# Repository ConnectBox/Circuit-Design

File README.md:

# Circuit-Design
Connectbox Circuit Design

This repo contains the schematic and KiCAD design files for the NEO-USB-HAT.  This is a daugherboard to add an extra USB port and power input to a NanoPi NEO.

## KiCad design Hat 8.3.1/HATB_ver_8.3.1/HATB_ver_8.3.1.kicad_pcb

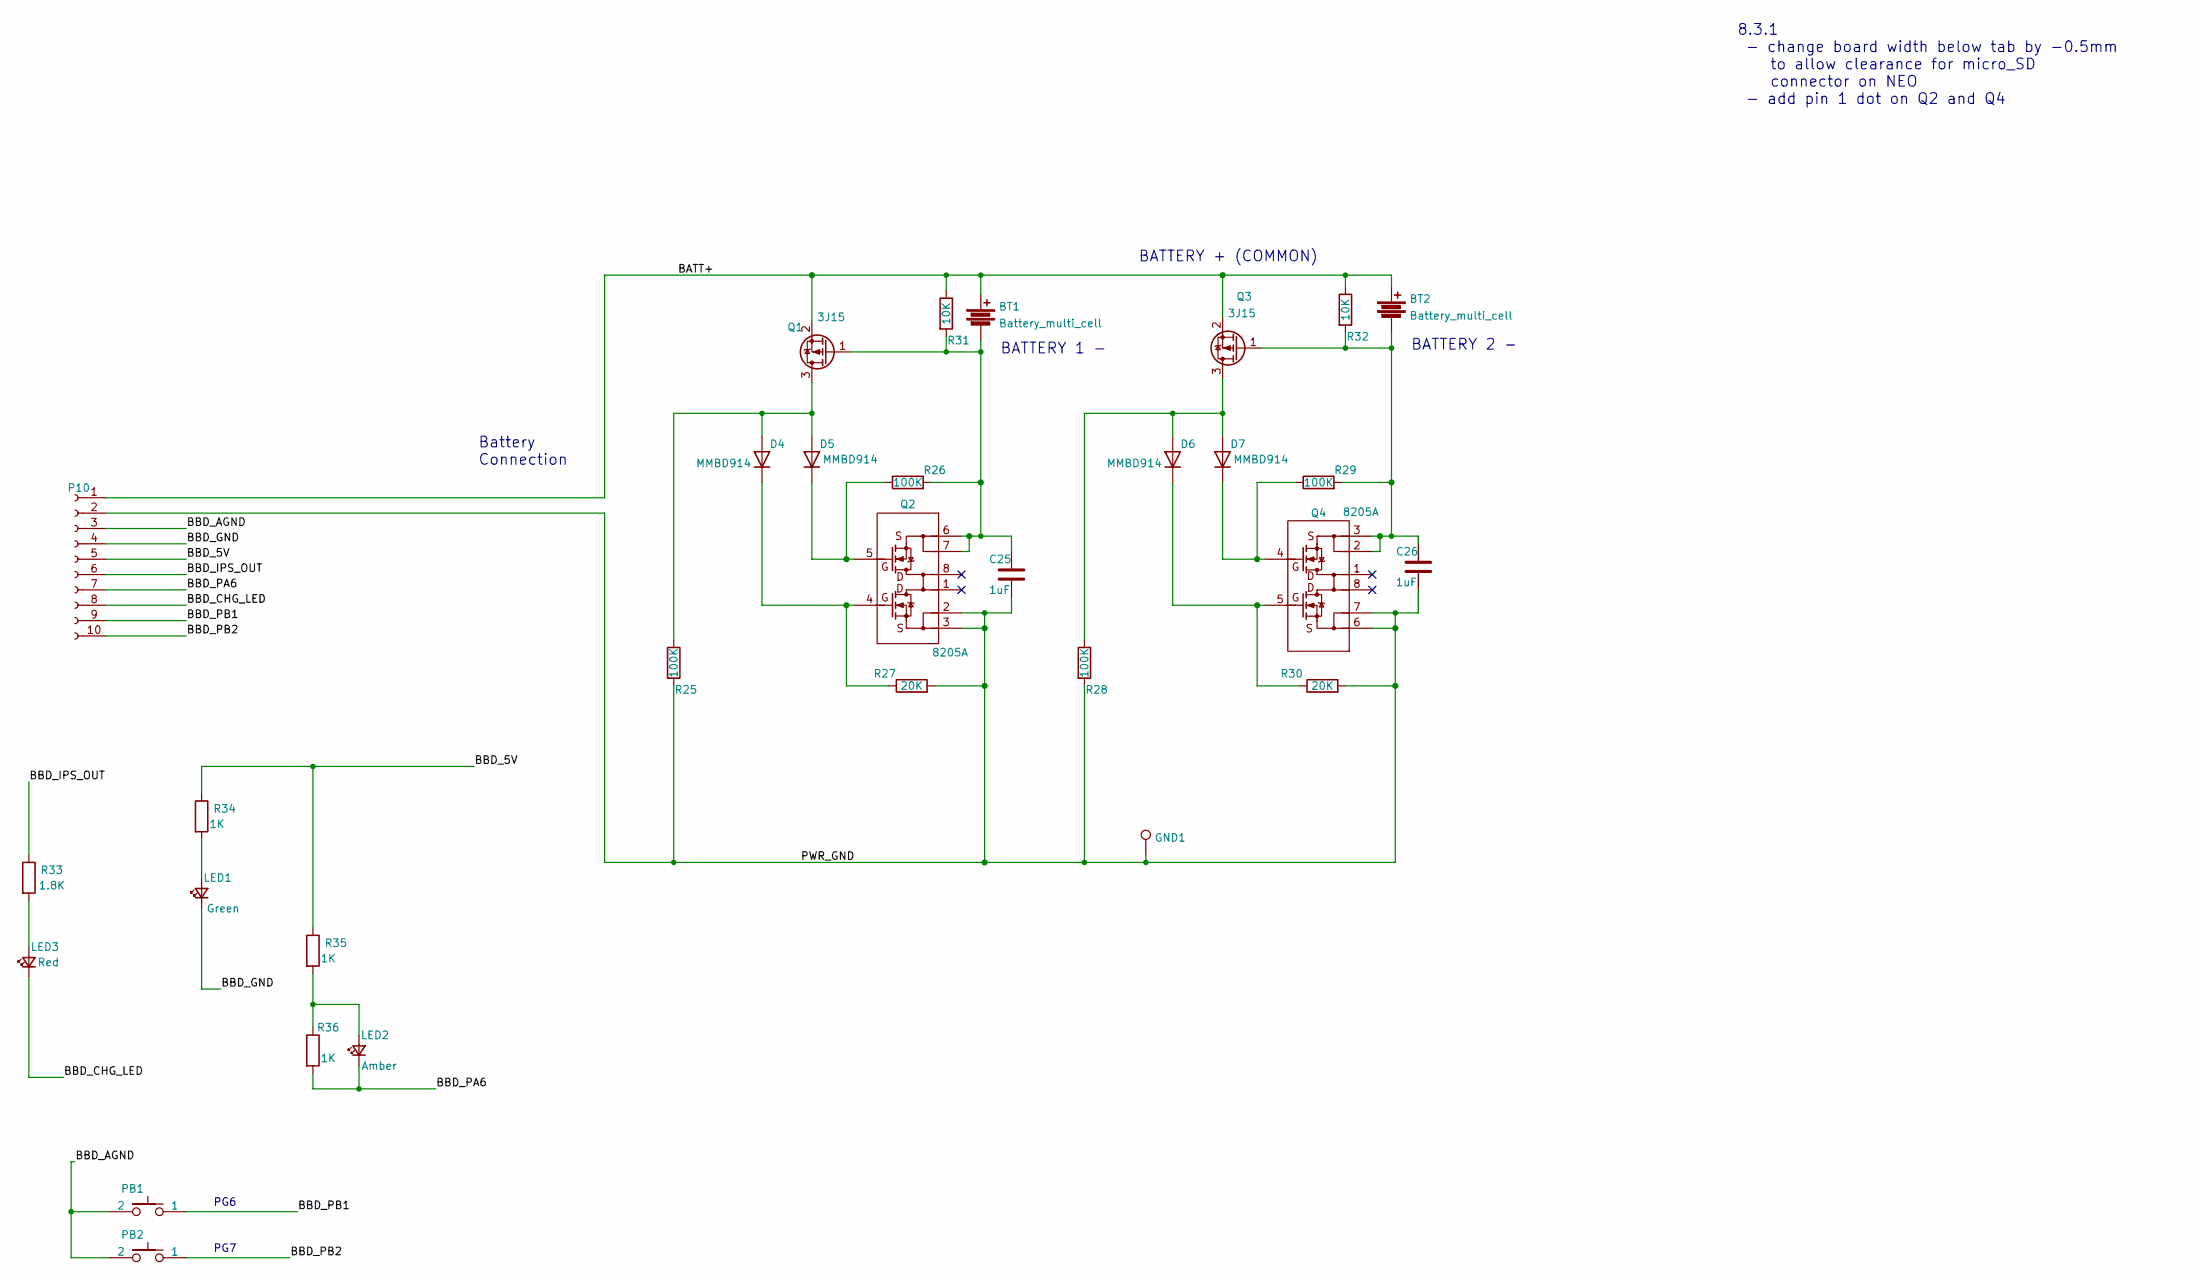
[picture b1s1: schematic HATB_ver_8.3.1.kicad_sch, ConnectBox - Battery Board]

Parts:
BT1, BT2: Battery_multi_cell; Battery 21700; Manufacturer P/N 109-2; DigiKey P/N 36-109-2-ND (2x)
C25, C26: 1uF; C_0805_2012Metric; Manufacturer P/N C0805C105K8PACTU; DigiKey P/N 399-8006-1-ND
D4, D5, D6, D7: MMBD914; D_SOT-23_ANK; Manufacturer P/N MMBD914LT1G; DigiKey P/N MMBD914LT1GOSCT-ND
GND1: TestPoint; TestPoint_THTPad_D1.5mm_Drill0.7mm
LED1: Green; LED_0603_1608Metric; Manufacturer P/N LTST-C191KFKT; DigiKey P/N 160-1446-1-ND
LED2: Amber; LED_0603_1608Metric; Manufacturer P/N LTST-C191KFKT; DigiKey P/N 160-1445-1-ND
LED3: Red; LED_0603_1608Metric; Manufacturer P/N LTST-C191KRKT; DigiKey P/N 160-1447-1-ND
P10: Conn_01x10_Female; PinSocket_2x05_P2.54mm_Vertical; Manufacturer P/N PPPC052LFBN-RC; DigiKey P/N S7108-ND
PB1, PB2: SPST-PUSH; SW-TL3305; Manufacturer P/N TL3305AF260QG; DigiKey P/N EG5353CT-ND
Q1, Q3: 3J15; SOT-323_SC-70; Manufacturer P/N SSM3J15FU,LF; DigiKey P/N SSM3J15FULFCT-ND
Q2, Q4: 8205A; 8305A; DigiKey P/N [none - from AliExpress|
R25, R26, R28, R29: 100K; R_0805_2012Metric; Manufacturer P/N RC0805FR-07100KL; DigiKey P/N 311-100KCRCT-ND
R27, R30: 20K; R_0805_2012Metric; Manufacturer P/N RC0805FR-0720KL; DigiKey P/N 311-20.0KCRCT-ND
R31, R32: 10K; R_0805_2012Metric; Manufacturer P/N RC0805FR-0710KL; DigiKey P/N 311-10KCRCT-ND
R33: 1.8K; R_0805_2012Metric; Manufacturer P/N RC0805FR-071K8L; DigiKey P/N 311-1.80KCRCT-ND
R34, R35, R36: 1K; R_0805_2012Metric; Manufacturer P/N RC0805FR-071KL; DigiKey P/N 311-1.00KCRCT-ND

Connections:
/BATT+: BT1.1, BT2.1, P10.1, Q1.2 (S), Q3.2 (S), R31.1, R32.1
/BBD_5V: P10.5, R34.1, R35.1
/BBD_AGND: P10.3, PB1.2, PB2.2
/BBD_CHG_LED: LED3.1 (K), P10.8
/BBD_GND: LED1.1 (K), P10.4
/BBD_IPS_OUT: P10.6, R33.1
/BBD_PA6: LED2.1 (K), P10.7, R36.2
/BBD_PB1: P10.9, PB1.1
/BBD_PB2: P10.10, PB2.1
/PWR_GND: C25.2, C26.2, GND1.1, P10.2, Q2.2 (S1), Q2.3 (S1), Q4.6 (S2), Q4.7 (S2), R25.2, R27.2, R28.2, R30.2
unnamed: BT1.2, C25.1, Q1.1 (G), Q2.6 (S2), Q2.7 (S2), R26.2, R31.2
unnamed: BT2.2, C26.1, Q3.1 (G), Q4.2 (S1), Q4.3 (S1), R29.2, R32.2
unnamed: D4.1 (K), Q2.4 (G1), R27.1
unnamed: D4.2 (A), D5.2 (A), Q1.3 (D), R25.1
unnamed: D5.1 (K), Q2.5 (G2), R26.1
unnamed: D6.1 (K), Q4.5 (G2), R30.1
unnamed: D6.2 (A), D7.2 (A), Q3.3 (D), R28.1
unnamed: D7.1 (K), Q4.4 (G1), R29.1
unnamed: LED1.2 (A), R34.2
unnamed: LED2.2 (A), R35.2, R36.1
unnamed: LED3.2 (A), R33.2

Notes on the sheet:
BATTERY + (COMMON)
PG7
BATTERY 1 -
Battery Connection
8.3.1 - change board width below tab by -0.5mm to allow clearance for micro_SD connector on NEO - add pin 1 dot on Q2 and Q4
PG6
BATTERY 2 -

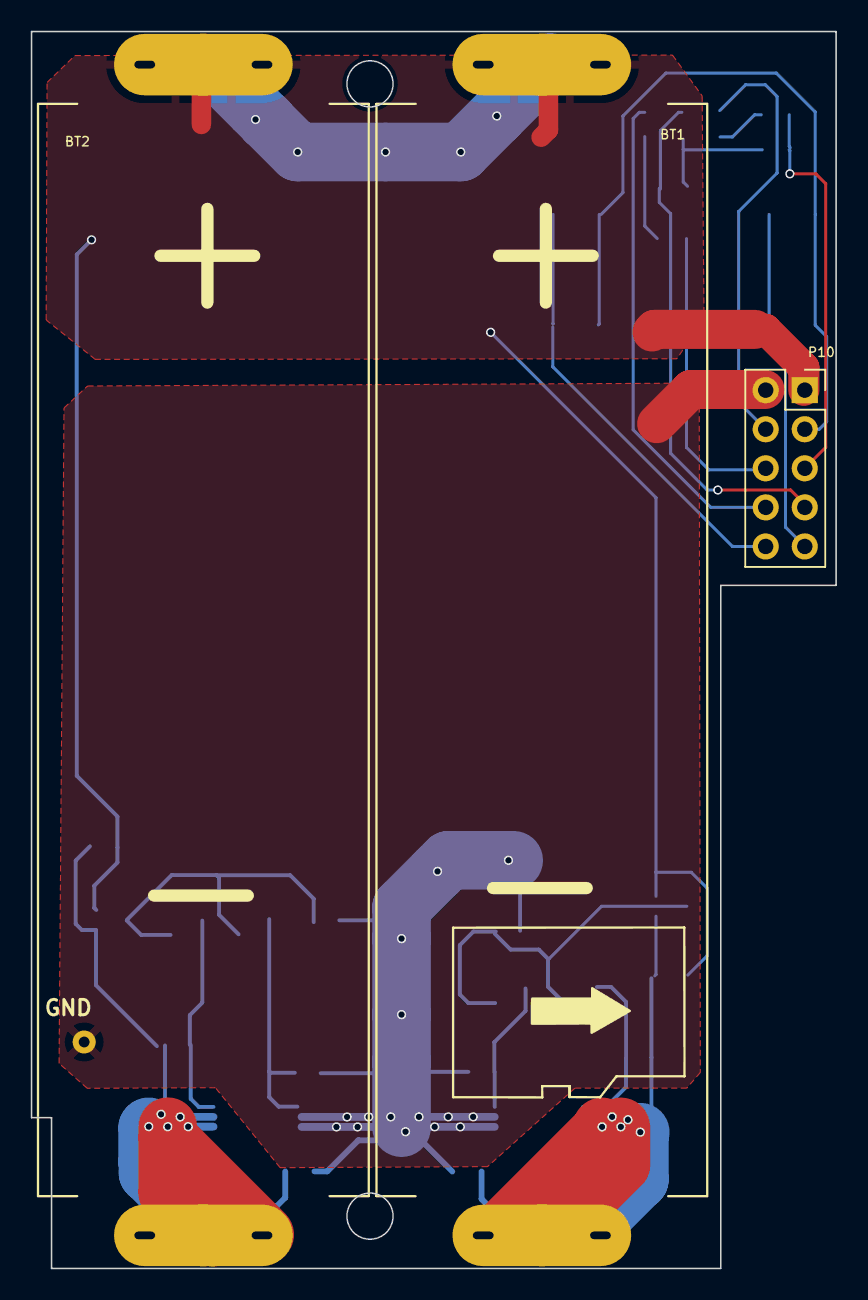
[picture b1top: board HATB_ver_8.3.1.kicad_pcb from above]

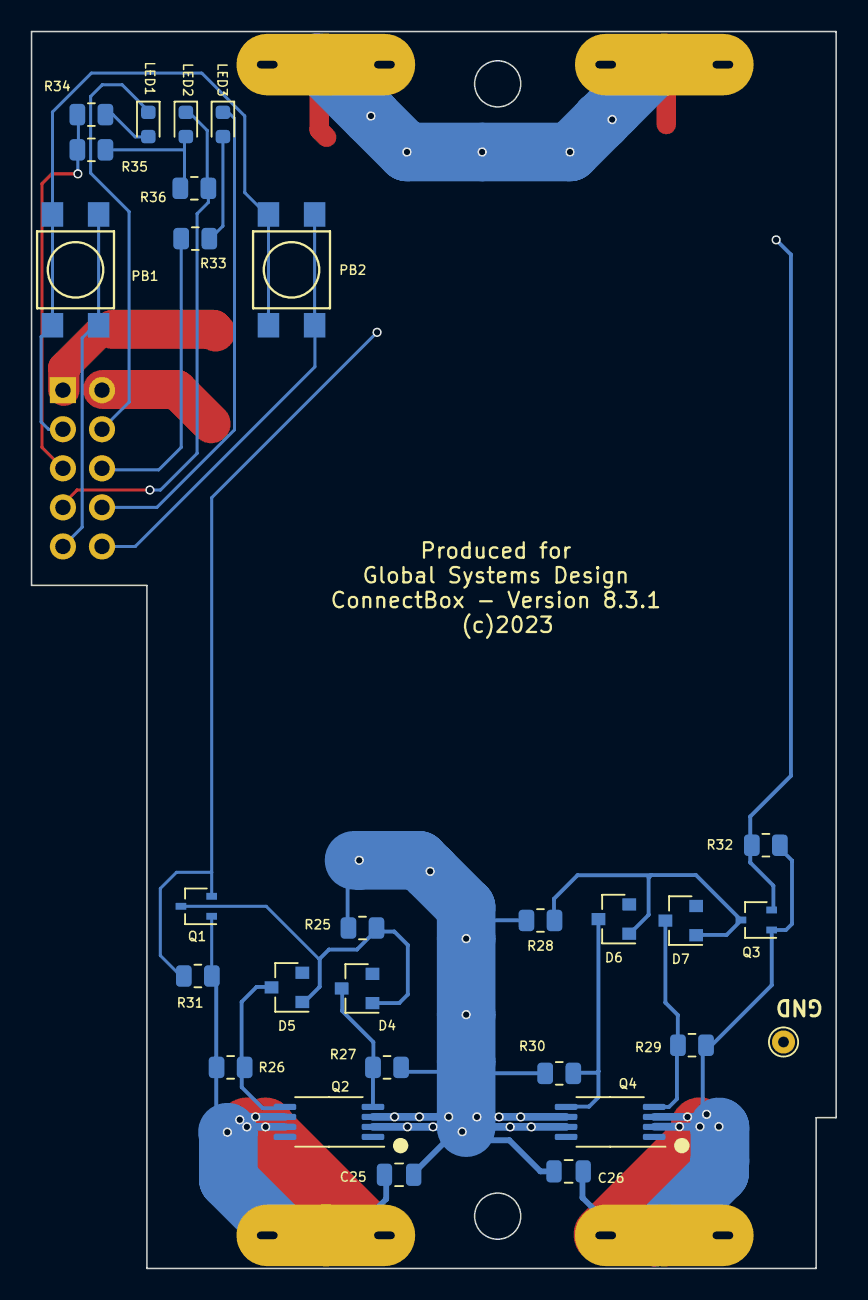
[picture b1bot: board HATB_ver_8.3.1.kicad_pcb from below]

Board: 2 copper layers, 52.3 x 80.4 mm, 31 parts (28 on the bottom side), 21 nets.

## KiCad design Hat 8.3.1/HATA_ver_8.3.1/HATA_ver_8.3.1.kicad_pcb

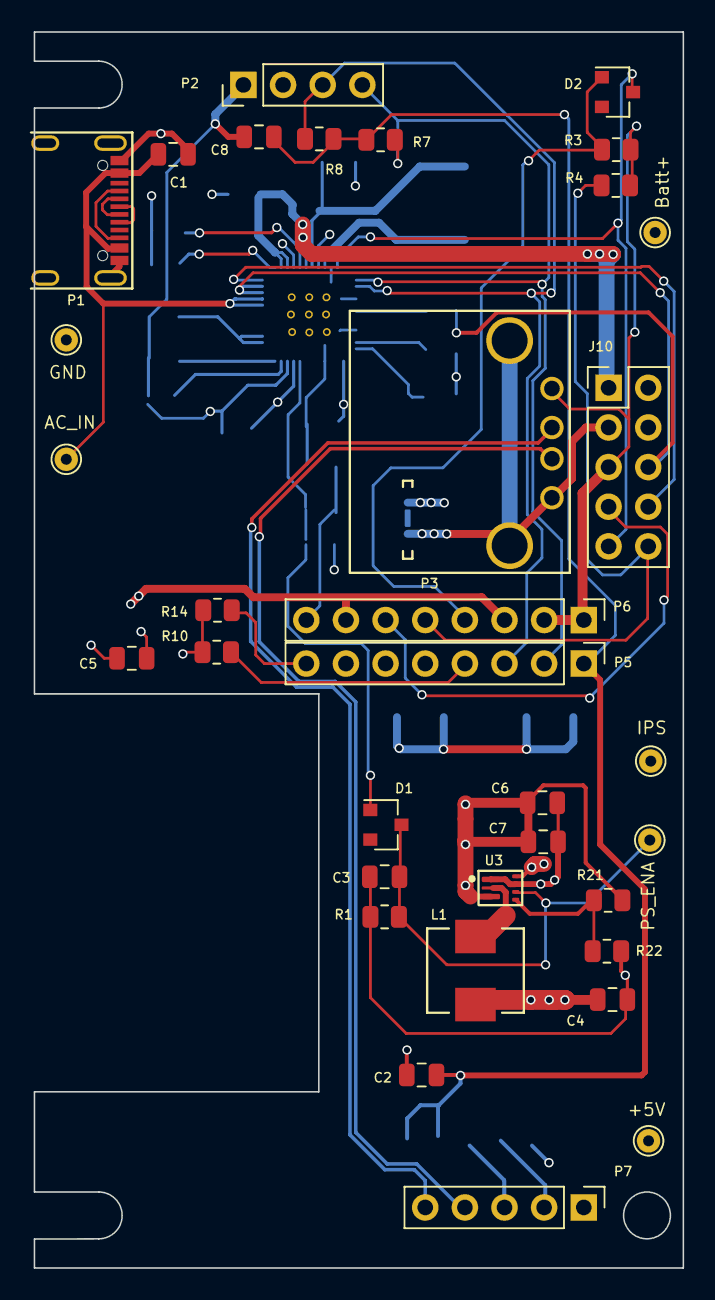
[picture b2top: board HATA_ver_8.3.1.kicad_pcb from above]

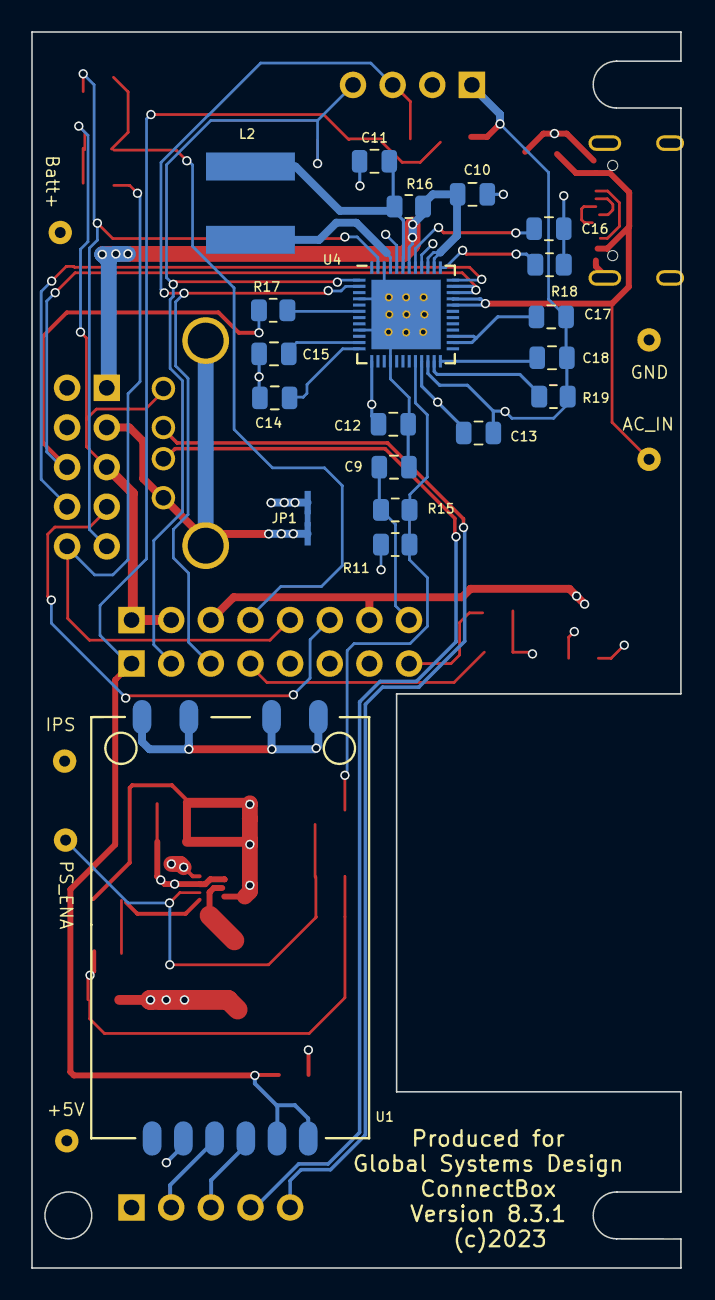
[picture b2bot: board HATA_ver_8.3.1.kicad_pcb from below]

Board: 4 copper layers, 41.6 x 79.2 mm, 54 parts (20 on the bottom side), 38 nets.

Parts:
C1, C2, C3, C5, C6, C7: 22uF; C_0805_2012Metric
C4: 10uf; C_0805_2012Metric
C8, C17, C18: 1uF; C_0805_2012Metric
C9, C10, C11, C12, C13: 10uF; C_0805_2012Metric
C14, C15, C16: 4.7uF; C_0805_2012Metric
D1, D2: MMBD914; D_SOT-23_ANK
J10: Conn_01x10_Female; PinHeader_2x05_P2.54mm_Vertical
JP1: Jumper; NetConnect-50
L1: 1.0 uH; INDUCTOR_SMD_5x5
L2: 4.7 uH; INDUCTOR_SMD_6x6-1
P1: USB-C; USB-C-GCT
P2: Conn_01x04; PinHeader_1x04_P2.54mm_Vertical
P3: USB_A_1; USB_A
P5, P6: Conn_01x08; PinHeader_1x08_P2.54mm_Vertical
P7: Conn_01x05; PinHeader_1x05_P2.54mm_Vertical
R1: 220K; R_0805_2012Metric
R3, R4, R17: 10K; R_0805_2012Metric
R7, R8, R10, R14: 2.2K; R_0805_2012Metric
R11: 51K; R_0805_2012Metric
R15: 1K; R_0805_2012Metric
R16: 0.03 ohm; R_0805_2012Metric
R18: 100; R_0805_2012Metric
R19: 200K; R_0805_2012Metric
R21: 732K; R_0805_2012Metric
R22: 100K; R_0805_2012Metric
TP1: Gnd; TestPoint_THTPad_D1.5mm_Drill0.7mm
TP2: IPS; TestPoint_THTPad_D1.5mm_Drill0.7mm
TP3: Ext_En; TestPoint_THTPad_D1.5mm_Drill0.7mm
TP4: 5V; TestPoint_THTPad_D1.5mm_Drill0.7mm
TP5: AC_IN; TestPoint_THTPad_D1.5mm_Drill0.7mm
TP6: Bat+; TestPoint_THTPad_D1.5mm_Drill0.7mm
U1: HC-R8812AF1; HC-R8812AU2-th-2
U3: TPS61022
U4: AXP209; UQFN-48-1EP_6x6mm_Pitch0.4mm_75

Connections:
/3v3: C2.1, C8.1, P5.1, R7.2, R8.2, U1.1 (PDN), U1.2 (3.3V)
/5V_FB: R21.2, R22.1, U3.4 (FB)
/5V_OUT: C5.1, C6.1, C7.1, J10.5, P2.2, P3.1 (VCC), P6.1, P6.2, P7.1, R3.2, R4.2, R11.1, R21.1, TP4.1, U3.3 (Vout)
/A_GND: C2.2, C5.2, C8.2, C13.1, C17.1, C18.1, J10.3, JP1.1, P2.1, P3.4 (GND), P3.5 (shield), P5.5, R10.2, R14.2, R19.1, U1.5 (GND), U1.7 (GND), U1.9 (GND), U1.10 (GND), U1.12 (GND), U4.22 (A_Gnd)
/BBD_CHG_LED: J10.8, U4.36 (ChgLED)
/BBD_IPS_OUT: C4.1, C12.1, C13.2, J10.6, L1.1, R17.2, TP2.1, U3.7 (VIN), U4.13 (LDO_24_In), U4.21 (APS), U4.34 (IPS_Out), U4.35 (IPS_Out), U4.40 (LDO_3_In), U4.44 (Vin_1)
/BBD_PA6: J10.7, P6.6
/BBD_PB1: D2.1 (K), J10.9, U4.47 (PwrON)
/BBD_PB2: J10.10, P6.5, R4.1
/PA3: P5.8, R14.1
/PG11: P5.4, R10.1
/Power control/AC_IN: C1.1, P1.A4/B9 (Power), P1.B4/A9 (Power), TP5.1, U4.32 (AC_IN), U4.33 (AC_IN)
/Power control/BATT+: C10.1, J10.1, R16.1, TP6.1, U4.38 (Batt), U4.39 (Batt), U4.42 (BatSense)
/Power control/EXT_EN: D1.2 (A), R11.2, R15.1, U4.20 (EXTEN)
/SCL: P2.3, P5.3, R8.1, U4.2 (SCK)
/SDA: P2.4, P5.2, R7.1, U4.1 (SDA)
/U2_SW: L1.2, U3.2 (SW)
/USB2_D+: P3.3 (D+), P7.4
/USB2_D-: P3.2 (D-), P7.5
GND: C1.2, C3.2, C4.2, C6.2, C7.2, C9.1, C10.2, C11.2, C12.2, C14.1, C15.1, C16.1, J10.2, J10.4, JP1.2, P1.1 (Shell), P1.A1/B12 (GND), P1.B1/A12 (GND), P6.3, P6.7, R1.2, R18.2, R22.2, TP1.1, U3.1 (GND), U3.6 (MODE), U4.4 (N_OE), U4.9 (PGnd_2), U4.16 (PGnd_3), U4.46 (PGnd_1), U4.49 (GND_PAD)
unnamed: C3.1, D1.1 (K), R1.1, TP3.1, U3.5 (ENA)
unnamed: C9.2, P6.8, R15.2
unnamed: C11.1, L2.1, R16.2, U4.43 (ChgSense)
unnamed: C14.2, U4.12 (LDO_2)
unnamed: C15.2, U4.11 (LDO_4)
unnamed: C16.2, U4.41 (LDO_3)
unnamed: C17.2, U4.26 (V_Internal), U4.27 (LDO_1_Set)
unnamed: C18.2, U4.24 (V_Ref)
unnamed: D2.2 (A), P6.4, R3.1
unnamed: L2.2, U4.45 (LX1)
unnamed: P1.A5 (CC1), P1.B5 (CC2)
unnamed: P1.A6 (D+), P1.B6 (D+)
unnamed: P1.A7 (D-), P1.B7 (D-)
unnamed: P7.2, U1.4 (DP+)
unnamed: P7.3, U1.3 (DM-)
unnamed: R17.1, U4.6 (N_VBus_En)
unnamed: R18.1, U4.37 (TS)
unnamed: R19.2, U4.23 (Bias)

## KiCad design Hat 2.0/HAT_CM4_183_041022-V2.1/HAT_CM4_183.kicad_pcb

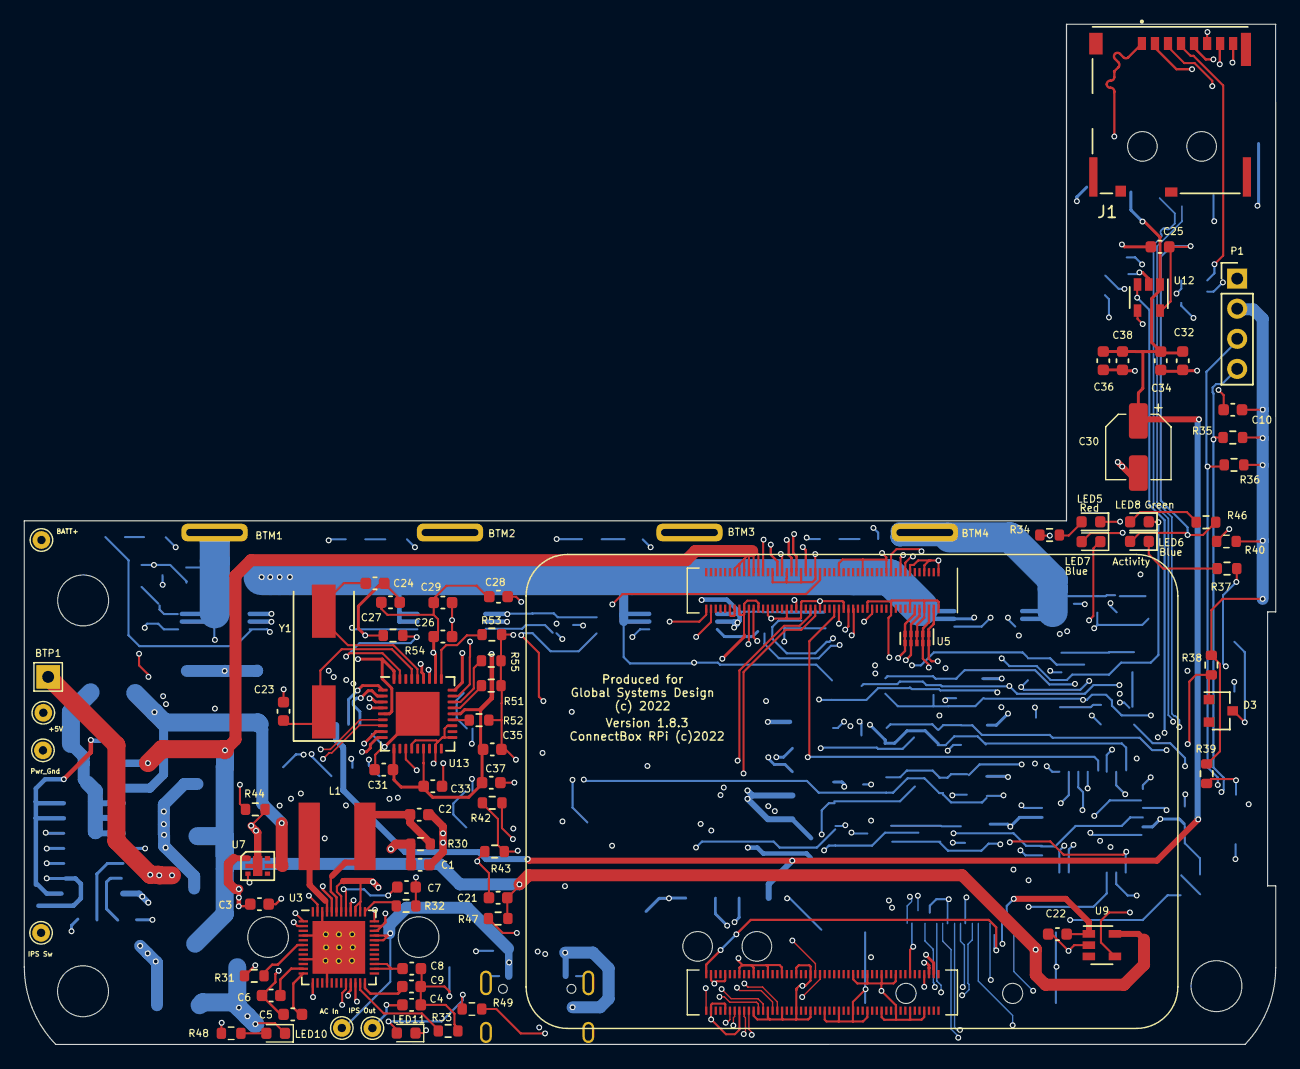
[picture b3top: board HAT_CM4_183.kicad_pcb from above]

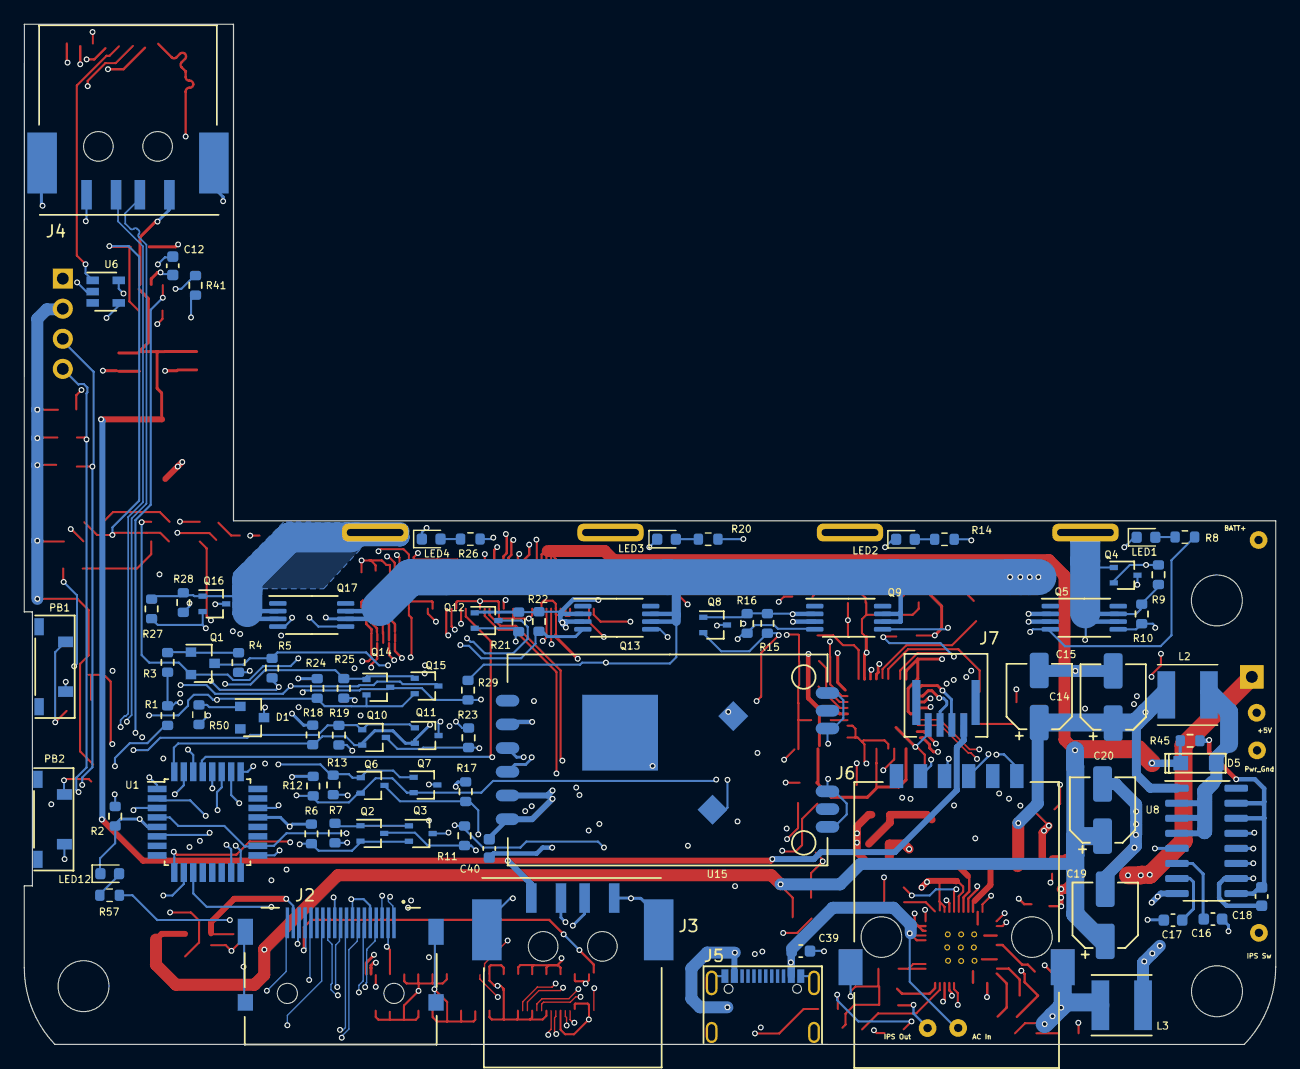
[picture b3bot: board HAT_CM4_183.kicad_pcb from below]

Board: 6 copper layers, 105.6 x 86.1 mm, 164 parts (81 on the bottom side), 124 nets.

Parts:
BTM1, BTM2, BTM3, BTM4: Conn_01x01_Female; WH-Battery-
BTP1: Conn_01x01_Female; TestPoint_THTPad_2.0x2.0mm_Drill1.0mm
C1, C2, C3, C4, C12, C25, C26, C27, C32, C34, C36, C38: 10uF; C_0603_1608Metric
C5, C6, C7: 4.7uF; C_0603_1608Metric
C8, C9, C10: 1uF; C_0603_1608Metric
C14, C15, C19, C20: 150uf; CP_Elec_5x3
C16: 1.0uf; C_0603_1608Metric
C17: 0.22uf; C_0603_1608Metric
C18, C21, C22, C28, C29, C31, C33, C35, C37: 0.1uf; C_0603_1608Metric
C23, C24: 9pF; C_0603_1608Metric
C30: 100uF; CP_Elec_5x3
C39, C40: 22uF; C_0603_1608Metric
D1, D3: MMBD914; D_SOT-23_ANK
D5: NRVTS260ESFT1G; SOD-123FL
H1, H2, H3: MountingHole; MountingHole_4.3mm_M4-A
J1: Micro_SD_Card; SDCARD_MOLEX_503398-1892
J2: 690-019-298-412; HDMI_CnC_SMT
J3, J4: USB_A; USB_A_CUI_smd
J5: USB-C; USB-C-GCT
J6: MagJack-S811; MagJack_S811
J7: Flex-4; SFW4R-1
L1: 4.7 uH; INDUCTOR_SMD_6x6-1
L2: 1.0 uH; L_Taiyo-Yuden_NR-50xx
L3: 1.5 uH; L_Taiyo-Yuden_NR-50xx
LED1, LED2, LED3, LED4, LED6, LED7, LED12: Blue; LED_0603_1608Metric
LED5: Red; LED_0603_1608Metric
LED8, LED10: Green; LED_0603_1608Metric
LED11: Amber; LED_0603_1608Metric
Module1: ComputeModule4; CM4_Module_noHoles
P1: Conn_01x04; PinHeader_1x04_P2.54mm_Vertical
PB1, PB2: SPST-PUSH; SW-TL3330A
Q1: 2N7002; SOT-23
Q2, Q3, Q4, Q6, Q7, Q8, Q10, Q11, Q12, Q14, Q15, Q16: 3J15; SOT-323_SC-70
Q5, Q9, Q13, Q17: 8205A; TSSOP-8_4.4x3mm_P0.65mm
R1, R6, R9, R12, R15, R18, R21, R24, R27, R31, R38, R39, R42: 10K; R_0603_1608Metric
R2, R3, R4, R11, R17, R23, R29, R50: 20K; R_0603_1608Metric
R5, R10, R13, R16, R19, R22, R25, R28, R44: 100K; R_0603_1608Metric
R7, R51, R52, R53, R55: 36K; R_0603_1608Metric
R8, R14, R20, R26, R40, R48, R49: 510; R_0603_1608Metric
R30: 0.03 ohm; R_0603_1608Metric
R32: 100; R_0603_1608Metric
R33: 200K; R_0603_1608Metric
R34: 1.8K; R_0603_1608Metric
R35, R36: 2.2K; R_0603_1608Metric
R37, R46, R57: 1K; R_0603_1608Metric
R41, R47, R54: 12K; R_0603_1608Metric
R43: 33K; R_0603_1608Metric
R45: 2.0; R_0603_1608Metric
TP1: AC_IN; TestPoint_THTPad_D1.5mm_Drill0.7mm
TP2: Pwr_Gnd; TestPoint_THTPad_D1.5mm_Drill0.7mm
TP3: Bat+; TestPoint_THTPad_D1.5mm_Drill0.7mm
TP4: IPS; TestPoint_THTPad_D1.5mm_Drill0.7mm
TP5: IPS_Sw; TestPoint_THTPad_D1.5mm_Drill0.7mm
TP6: 5V; TestPoint_THTPad_D1.5mm_Drill0.7mm
U1: ATtiny88-AU; TQFP-32_7x7mm_P0.8mm
U3: AXP209; UQFN-48-1EP_6x6mm_Pitch0.4mm_75
U5: TPD4EUSB30; USON-10_2.5x1.0mm_P0.5mm
U6, U9, U12: RT9742ANGJ5F; SOT-23-5
U7: AP22814A; U-DFN2020-6
U8: MAX1709ESE; SOP-16_3.9x9.9mm_P1.27mm
U13: USB2514B-I/M2; QFN-36-1EP_6x6mm_P0.5mm_EP3.7x3.7mm
U15: HC-R8812AF1; HC-R8812AU2
Y1: 24MHz; Crystal_SMD_HC49-SD

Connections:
+3.3v: C10.1, C26.1, C27.1, C28.1, C29.1, C31.1, C33.1, C35.1, C37.1, C40.1, Module1.78 (GPIO_VREF(1.8v/3.3v_Input)), Module1.84 (+3.3v_(Output)), Module1.86 (+3.3v_(Output)), P1.2, R35.2, R36.2, R38.2, R39.2, R40.1, R41.2, U6.5 (VIN), U13.5 (VDDA33), U13.10 (VDDA33), U13.15 (VDD33), U13.23 (VDD33), U13.27 (VBUS_DET), U13.29 (VDDA33), U13.36 (VDDA33), U15.1 (PDN), U15.2 (3.3V)
+5V: C19.1, C20.1, C21.1, C25.1, D5.1 (K), LED6.2 (A), Module1.77 (+5v_(Input)), Module1.79 (+5v_(Input)), Module1.81 (+5v_(Input)), Module1.83 (+5v_(Input)), Module1.85 (+5v_(Input)), Module1.87 (+5v_(Input)), R4.1, R45.1, R46.1, R47.2, TP6.1, U9.5 (VIN), U12.5 (VIN)
/AC_IN: C39.1, J5.A4/B9 (Power), J5.B4/A9 (Power), R1.2, R3.1, TP1.1, U3.32 (AC_IN), U3.33 (AC_IN)
/Batteries/BT1-: BTM1.1, Q4.1 (G), Q5.6 (S2), Q5.7 (S2), R7.1, R9.1, R10.2
/Batteries/BT2-: BTM2.1, Q8.1 (G), Q9.2 (S1), Q9.3 (S1), R15.1, R16.2
/Batteries/BT3-: BTM3.1, Q12.1 (G), Q13.2 (S1), Q13.3 (S1), R21.1, R22.2
/Batteries/BT4-: BTM4.1, Q16.1 (G), Q17.2 (S1), Q17.3 (S1), R27.1, R28.2
/Battery/5V_OVR: D1.1 (K), R44.1, U1.10 (PD6), U7.3 (ENA)
/Battery/AXP_EXTEN: R50.1, U1.2 (PD4), U3.20 (EXTEN)
/Battery/BATT+: BTP1.1, C1.1, Q4.2 (S), Q8.2 (S), Q12.2 (S), Q16.2 (S), R5.1, R9.2, R13.1, R15.2, R19.1, R21.2, R25.1, R27.2, R30.1, TP3.1, U1.4 (VCC), U1.18 (AVCC), U3.38 (Batt), U3.39 (Batt), U3.42 (BatSense)
/Battery/BT1_PRES: Q2.2 (S), Q3.2 (S), Q4.3 (D), R6.1, U1.30 (PD0)
/Battery/BT2_PRES: Q6.2 (S), Q7.2 (S), Q8.3 (D), R12.1, U1.31 (PD1)
/Battery/BT3_PRES: Q10.2 (S), Q11.2 (S), Q12.3 (D), R18.1, U1.32 (PD2)
/Battery/BT4_PRES: Q14.2 (S), Q15.2 (S), Q16.3 (D), R24.1, U1.1 (PD3)
/Battery/HEARTBEAT: R57.2, U1.26 (PC3)
/Battery/I2C_SCL: Module1.80 (SCL0), P1.3, R36.1, U1.28 (PC5), U3.2 (SCK)
/Battery/I2C_SDA: Module1.82 (SDA0), P1.4, R35.1, U1.27 (PC4), U3.1 (SDA)
/Battery/MISO: Module1.40 (GPIO9), U1.16 (PB4)
/Battery/MOSI: Module1.44 (GPIO10), U1.15 (PB3)
/Battery/PB_IN: D3.1 (K), PB1.1, U1.11 (PD7), U3.47 (PwrON)
/Battery/PWR_IRQ: R42.1, U1.9 (PD5)
/Battery/SCL: Module1.38 (GPIO11), U1.17 (PB5)
/Battery//BT1_ENA_B: Q2.1 (G), Q3.1 (G), R7.2
/Battery//BT2_ENA: Q6.1 (G), Q7.1 (G), R13.2, U1.22 (PA1)
/Battery//BT3_ENA: Q10.1 (G), Q11.1 (G), R19.2, U1.3 (PA2)
/Battery//BT4_ENA: Q14.1 (G), Q15.1 (G), R25.2, U1.6 (PA3)
/Battery//RESET: Module1.46 (GPIO22), U1.29 (~RESET/PC6)
/CM4_GPIO/+1.8v: Module1.88 (+1.8v_(Output)), Module1.90 (+1.8v_(Output))
/CM4_GPIO/ETH_LEDG: Module1.17 (Ethernet_nLED2(3.3v)), R48.1
/CM4_GPIO/ETH_LEDY: Module1.15 (Ethernet_nLED3(3.3v)), R49.1
/CM4_GPIO/GPIO6: LED7.1 (K), Module1.30 (GPIO6)
/CM4_GPIO/GPIO_IRQ: Module1.51 (GPIO15), R42.2, R43.2
/CM4_GPIO/GPIO_PB1: D3.2 (A), Module1.56 (GPIO3), R38.1
/CM4_GPIO/GPIO_PB2: Module1.54 (GPIO4), PB2.1, R39.1
/CM4_GPIO/PI_nLED_Activity: Module1.21 (PI_nLED_Activity), R37.1
/CM4_GPIO/SD_CLK: J1.5 (CLK), Module1.57 (SD_CLK)
/CM4_GPIO/SD_CMD: J1.3 (CMD), Module1.62 (SD_CMD)
/CM4_GPIO/SD_DAT0: J1.7 (DAT0), Module1.63 (SD_DAT0)
/CM4_GPIO/SD_DAT1: J1.8 (DAT1), Module1.67 (SD_DAT1)
/CM4_GPIO/SD_DAT2: J1.1 (DAT2), Module1.69 (SD_DAT2)
/CM4_GPIO/SD_DAT3: J1.2 (DAT3/CD), Module1.61 (SD_DAT3)
/CM4_GPIO/SD_PWR: C12.1, J1.4 (VDD), U6.1 (VOUT)
/CM4_GPIO/SD_PWR_ON: Module1.75 (SD_PWR_ON), R41.1, U6.4 (EN)
/CM4_GPIO/TRD0_N: J6.3 (TD-), Module1.10 (Ethernet_Pair0_N), U5.4 (D2+), U5.7
/CM4_GPIO/TRD0_P: J6.1 (TD+), Module1.12 (Ethernet_Pair0_P), U5.5 (D2-), U5.6
/CM4_GPIO/TRD1_N: J6.5 (RD-), Module1.6 (Ethernet_Pair1_N), U5.2 (D1-), U5.9
/CM4_GPIO/TRD1_P: J6.4 (RD+), Module1.4 (Ethernet_Pair1_P), U5.1 (D1+), U5.10
/CM4_HighSpeed/HDMI0_CEC: J2.13 (CEC), Module1.151 (HDMI0_CEC)
/CM4_HighSpeed/HDMI0_CK_N: J2.12 (CK-), Module1.190 (HDMI0_CLK_N)
/CM4_HighSpeed/HDMI0_CK_P: J2.10 (CK+), Module1.188 (HDMI0_CLK_P)
/CM4_HighSpeed/HDMI0_D0_N: J2.9 (D0-), Module1.184 (HDMI0_TX0_N)
/CM4_HighSpeed/HDMI0_D0_P: J2.7 (D0+), Module1.182 (HDMI0_TX0_P)
/CM4_HighSpeed/HDMI0_D1_N: J2.6 (D1-), Module1.178 (HDMI0_TX1_N)
/CM4_HighSpeed/HDMI0_D1_P: J2.4 (D1+), Module1.176 (HDMI0_TX1_P)
/CM4_HighSpeed/HDMI0_D2_N: J2.3 (D2-), Module1.172 (HDMI0_TX2_N)
/CM4_HighSpeed/HDMI0_D2_P: J2.1 (D2+), Module1.170 (HDMI0_TX2_P)
/CM4_HighSpeed/HDMI0_HOTPLUG: J2.19 (HPD/HEAC-), Module1.153 (HDMI0_HOTPLUG)
/CM4_HighSpeed/HDMI0_SCL: J2.15 (SCL), Module1.200 (HDMI0_SCL)
/CM4_HighSpeed/HDMI0_SDA: J2.16 (SDA), Module1.199 (HDMI0_SDA)
/CM4_HighSpeed/HDMI_5v: C22.1, J2.18 (+5V), U9.1 (VOUT)
/CM4_HighSpeed/USB2_N: Module1.103 (USB2_N), U13.31 (USBDP_UP)
/CM4_HighSpeed/USB2_P: Module1.105 (USB2_P), U13.30 (USBDM_UP)
/Charger/IPS_OUT: C3.1, C4.1, R31.2, R34.1, TP4.1, U3.13 (LDO_24_In), U3.21 (APS), U3.34 (IPS_Out), U3.35 (IPS_Out), U3.40 (LDO_3_In), U3.44 (Vin_1), U7.1 (Vin)
/Power/IPS_SW: C14.1, C15.1, L2.1, TP5.1, U7.5 (Vout), U8.1 (ONA)
/USB Hub/HD1_N: J7.2, U13.1 (USBDM_DN1/PRT_DIS_M1)
/USB Hub/HD1_P: J7.3, U13.2 (USBDP_DN1/PRT_DIS_P1)
/USB Hub/HD2_N: U13.3 (USBDM_DN2/PRT_DIS_M2), U15.3 (DM-)
/USB Hub/HD2_P: U13.4 (USBDP_DN2/PRT_DIS_P2), U15.4 (DP+)
/USB Hub/HD3_N: J4.2 (D-), U13.6 (USBDM_DN3/PRT_DIS_M3)
/USB Hub/HD3_P: J4.3 (D+), U13.7 (USBDP_DN3/PRT_DIS_P3)
/USB Hub/HD4_N: J3.2 (D-), U13.8 (USBDM_DN4/PRT_DIS_M4)
/USB Hub/HD4_P: J3.3 (D+), U13.9 (USBDP_DN4/PRT_DIS_P4)
/USB Hub/PWR1: U12.4 (EN), U13.12 (PRTPWR1/BC_EN1)
/USB Hub/VBUS: C30.1, C32.1, C34.1, C36.1, C38.1, J3.1 (VBUS), J4.1 (VBUS), J7.1, U12.1 (VOUT)
/USB Hub/nEXTRST: Module1.100 (nEXTRST), U13.26 (RESET_N)
/USB Hub/nOCS1: U12.3 (/FLG), U13.13 (OCS_N1), U13.17 (OCS_N2), U13.19 (OCS_N3), U13.21 (OCS_N4)
GND: C4.2, C8.1, C9.1, C10.2, C12.2, C21.2, C22.2, C23.2, C24.2, C25.2, C26.2, C27.2, C28.2, C29.2, C30.2, C31.2, C32.2, C33.2, C34.2, C35.2, C36.2, C37.2, C38.2, C39.2, C40.2, J1.6 (VSS), J2.2 (D2S), J2.5 (D1S), J2.8 (D0S), J2.11 (CKS), J2.17 (GND), J2.SH1 (SH), J2.SH2 (SH), J2.SH3 (SH), J2.SH4 (SH), J3.4 (GND), J3.5 (Shield), J4.4 (GND), J4.5 (Shield), J5.1 (Shell), J5.A1/B12 (GND), J5.B1/A12 (GND), J6.7 (Shield), J7.4, L3.2, LED10.1 (K), LED11.1 (K), Module1.1 (GND), Module1.2 (GND), Module1.7 (GND), Module1.8 (GND), Module1.13 (GND), Module1.14 (GND), Module1.22 (GND), Module1.23 (GND), Module1.32 (GND), Module1.33 (GND), Module1.42 (GND), Module1.43 (GND), Module1.52 (GND), Module1.53 (GND), Module1.59 (GND), Module1.60 (GND), Module1.65 (GND), Module1.66 (GND), Module1.71 (GND), Module1.74 (GND), Module1.98 (GND), Module1.107 (GND), Module1.108 (GND), Module1.113 (GND), Module1.114 (GND), Module1.119 (GND), Module1.120 (GND), Module1.125 (GND), Module1.126 (GND), Module1.131 (GND), Module1.132 (GND), Module1.137 (GND), Module1.138 (GND), Module1.144 (GND), Module1.150 (GND), Module1.155 (GND), Module1.156 (GND), Module1.161 (GND), Module1.162 (GND), Module1.167 (GND), Module1.168 (GND), Module1.173 (GND), Module1.174 (GND), Module1.179 (GND), Module1.180 (GND), Module1.185 (GND), Module1.186 (GND), Module1.191 (GND), Module1.192 (GND), Module1.197 (GND), Module1.198 (GND), P1.1, PB1.2, PB2.2, R33.1, R43.1, R51.2, R52.2, R53.2, R54.1, R55.2, U3.22 (A_Gnd), U5.3 (GND), U5.8 (GND), U6.2 (GND), U9.2 (GND), U12.2 (GND), U13.37 (VSS), U15.5 (GND), U15.7 (GND), U15.9 (GND), U15.10 (GND), U15.12 (GND), U15.13 (GND), U15.14 (GND), U15.15 (GND)
unnamed: C2.1, L1.1, R30.2, U3.43 (ChgSense)
unnamed: C5.2, U3.12 (LDO_2)
unnamed: C6.2, U3.11 (LDO_4)
unnamed: C7.2, U3.41 (LDO_3)
unnamed: C8.2, U3.26 (V_Internal), U3.27 (LDO_1_Set)
unnamed: C9.2, U3.24 (V_Ref)
unnamed: C16.1, U8.6 (SS/LIM)
unnamed: C17.1, U8.7 (REF)
unnamed: C18.1, R45.2, U8.9 (OUT), U8.14 (_3.3/5), U8.15 (CLK)
unnamed: C23.1, U13.33 (XTALIN/CLKIN), Y1.1
unnamed: C24.1, U13.32 (XTALOUT), Y1.2
unnamed: D1.2 (A), R50.2
unnamed: D5.2 (A), L2.2, U8.2 (LX), U8.3 (LX), U8.4 (LX)
unnamed: L1.2, U3.45 (LX1)
unnamed: LED1.1 (K), LED2.1 (K), LED3.1 (K), LED4.1 (K), Q1.3 (D), R5.2
unnamed: LED1.2 (A), R8.2
unnamed: LED2.2 (A), R14.2
unnamed: LED3.2 (A), R20.2
unnamed: LED4.2 (A), R26.2
unnamed: LED5.1 (K), U3.36 (ChgLED)
unnamed: LED5.2 (A), R34.2
unnamed: LED6.1 (K), R37.2
unnamed: LED8.2 (A), R46.2
unnamed: LED10.2 (A), R48.2
unnamed: LED11.2 (A), R49.2
unnamed: LED12.2 (A), R57.1
unnamed: Q1.1 (G), R3.2, R4.2
unnamed: Q2.3 (D), Q5.4 (G1), R8.1, R11.1
unnamed: Q3.3 (D), Q5.5 (G2), R10.1
unnamed: Q6.3 (D), Q9.5 (G2), R14.1, R17.1
unnamed: Q7.3 (D), Q9.4 (G1), R16.1
unnamed: Q10.3 (D), Q13.5 (G2), R20.1, R23.1
unnamed: Q11.3 (D), Q13.4 (G1), R22.1
unnamed: Q14.3 (D), Q17.5 (G2), R26.1, R29.1
unnamed: Q15.3 (D), Q17.4 (G1), R28.1
unnamed: R1.1, R2.1, U1.25 (PC2)
unnamed: R31.1, U3.6 (N_VBus_En)
unnamed: R32.1, U3.37 (TS)
unnamed: R33.2, U3.23 (Bias)
unnamed: LED7.2 (A), R40.2
unnamed: R47.1, U9.4 (EN)
unnamed: R51.1, U13.24 (SCL/SMBCLK/CFG_SEL0)
unnamed: R52.1, U13.22 (SDA/SMBDATA/NON_REM1)
unnamed: R53.1, U13.28 (SUSP_IND/LOCAL_PWR/NON_REM0)
unnamed: R54.2, U13.35 (RBIAS)
unnamed: R55.1, U13.25 (HS_IND/CFG_SEL1)
PWR_GND: C1.2, C2.2, C3.2, C5.1, C6.1, C7.1, C14.2, C15.2, C16.2, C17.2, C18.2, C19.2, C20.2, L3.1, LED8.1 (K), LED12.1 (K), Q1.2 (S), Q5.2 (S1), Q5.3 (S1), Q9.6 (S2), Q9.7 (S2), Q13.6 (S2), Q13.7 (S2), Q17.6 (S2), Q17.7 (S2), R2.2, R6.2, R11.2, R12.2, R17.2, R18.2, R23.2, R24.2, R29.2, R32.2, R44.2, TP2.1, U1.5 (GND), U1.21 (GND), U3.4 (N_OE), U3.9 (PGnd_2), U3.16 (PGnd_3), U3.46 (PGnd_1), U3.49 (GND_PAD), U7.2 (GND), U8.5 (GND), U8.8 (GND), U8.10 (FB), U8.11 (PGND), U8.12 (PGND), U8.13 (PGND)

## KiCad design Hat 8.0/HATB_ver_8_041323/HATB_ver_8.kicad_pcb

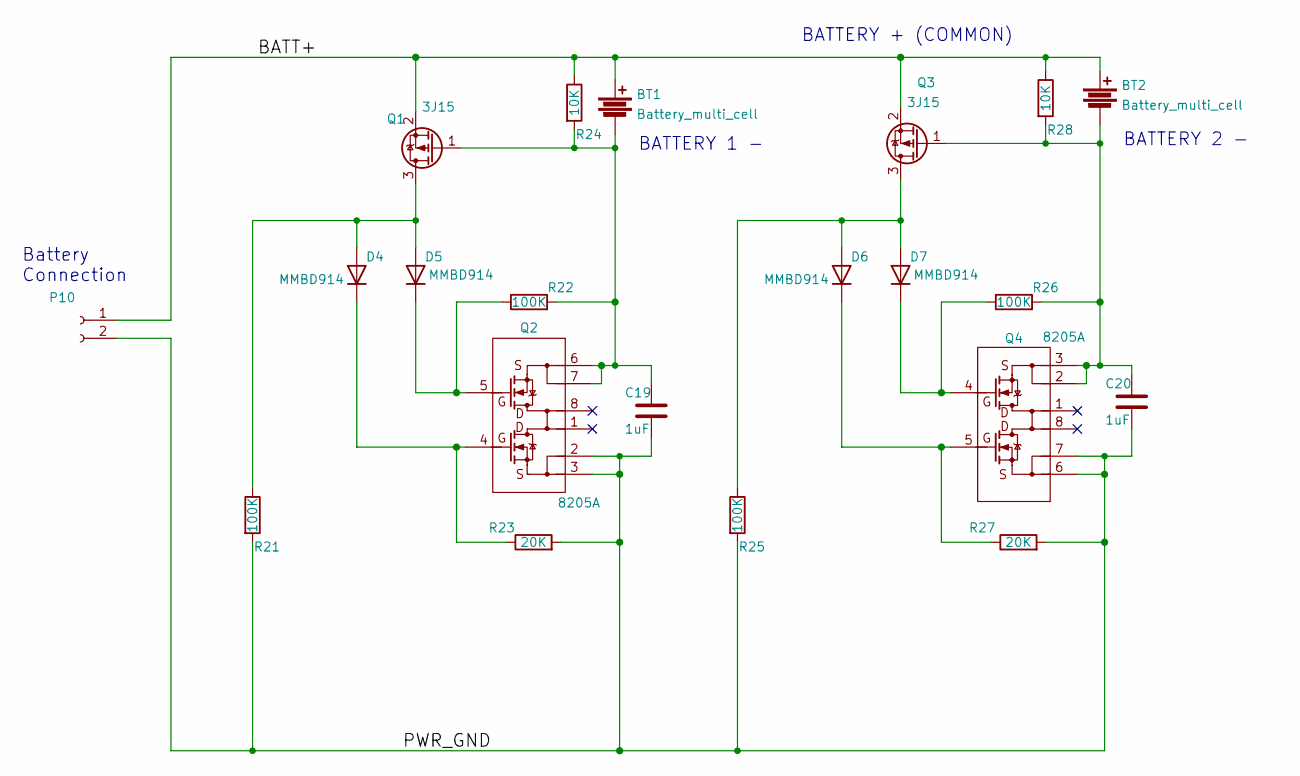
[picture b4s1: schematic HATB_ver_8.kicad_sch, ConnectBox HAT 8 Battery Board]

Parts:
BT1, BT2: Battery_multi_cell; Battery 21700
C19, C20: 1uF; C_0805_2012Metric; Manufacturer P/N C0805C105K8PACTU; DigiKey P/N 399-8006-1-ND
D4, D5, D6, D7: MMBD914; D_SOT-23_ANK; Manufacturer P/N MMBD914LT1G; DigiKey P/N MMBD914LT1GOSCT-ND
P10: Conn_01x02_Female; PinSocket_1x02_P2.54mm_Vertical
Q1, Q3: 3J15; SOT-323_SC-70; Manufacturer P/N SSM3J15FU,LF; DigiKey P/N SSM3J15FULFCT-ND
Q2, Q4: 8205A; TSSOP-8_4.4x3mm_P0.65mm; DigiKey P/N [none - from AliExpress|
R21, R22, R25, R26: 100K; R_0603_1608Metric; Manufacturer P/N RC0603FR-07100KL; DigiKey P/N 311-100KHRCT-ND
R23, R27: 20K; R_0603_1608Metric; Manufacturer P/N RC0603FR-0720KL; DigiKey P/N 311-20.0KHRCT-ND
R24, R28: 10K; R_0603_1608Metric; Manufacturer P/N RC0603FR-0710KL; DigiKey P/N 311-10KHRCT-ND

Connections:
/BATT+: BT1.1, BT2.1, P10.1, Q1.2 (S), Q3.2 (S), R24.1, R28.1
/PWR_GND: C19.2, C20.2, P10.2, Q2.2 (S1), Q2.3 (S1), Q4.6 (S2), Q4.7 (S2), R21.2, R23.2, R25.2, R27.2
unnamed: BT1.2, C19.1, Q1.1 (G), Q2.6 (S2), Q2.7 (S2), R22.2, R24.2
unnamed: BT2.2, C20.1, Q3.1 (G), Q4.2 (S1), Q4.3 (S1), R26.2, R28.2
unnamed: D4.1 (K), Q2.4 (G1), R23.1
unnamed: D4.2 (A), D5.2 (A), Q1.3 (D), R21.1
unnamed: D5.1 (K), Q2.5 (G2), R22.1
unnamed: D6.1 (K), Q4.5 (G2), R27.1
unnamed: D6.2 (A), D7.2 (A), Q3.3 (D), R25.1
unnamed: D7.1 (K), Q4.4 (G1), R26.1

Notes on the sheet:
BATTERY + (COMMON)
BATTERY 1 -
Battery Connection
BATTERY 2 -

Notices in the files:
Hat 8.3.1/HATA_ver_8.3.1/HATA_ver_8.3.1.kicad_pcb:
(c)2023
Hat_7.0.6/HAT_ver_7.0.6/HAT_ver_7.kicad_pcb:
Copyright 2021
